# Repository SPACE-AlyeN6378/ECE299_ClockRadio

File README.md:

# Raspberry Pi Pico: Clock Radio
Clock radio is driven by Raspberry Pi Pico
## Configuration
### NORMAL MODE

- Button 1 - Mute
- Button 2 - Toggle 12-24 hour format
- Button 3 - Set time
- Button 4 - Set alarm
- Rotary button - Toggle between changing frequency/Volume 
- Turn knob - Change frequency/volume

### SET TIME MODE

- Button 1 - Menu Left
- Button 2 - Menu Right 
- Button 3 - Cancel
- Button 4 - Cancel setting & change alarm
- Rotary button - Confirm
- Turn knob - Change time

### SET ALARM MODE

- Button 1 - Menu Left
- Button 2 - Menu Right 
- Button 3 - Time settings
- Button 4 - Alarm on/off
- Rotary button - Confirm and exit
- Turn knob - Change alarm time

### WHILE ALARM IS RINGING

- Button 1 - Stop alarm
- Button 2 - Snooze

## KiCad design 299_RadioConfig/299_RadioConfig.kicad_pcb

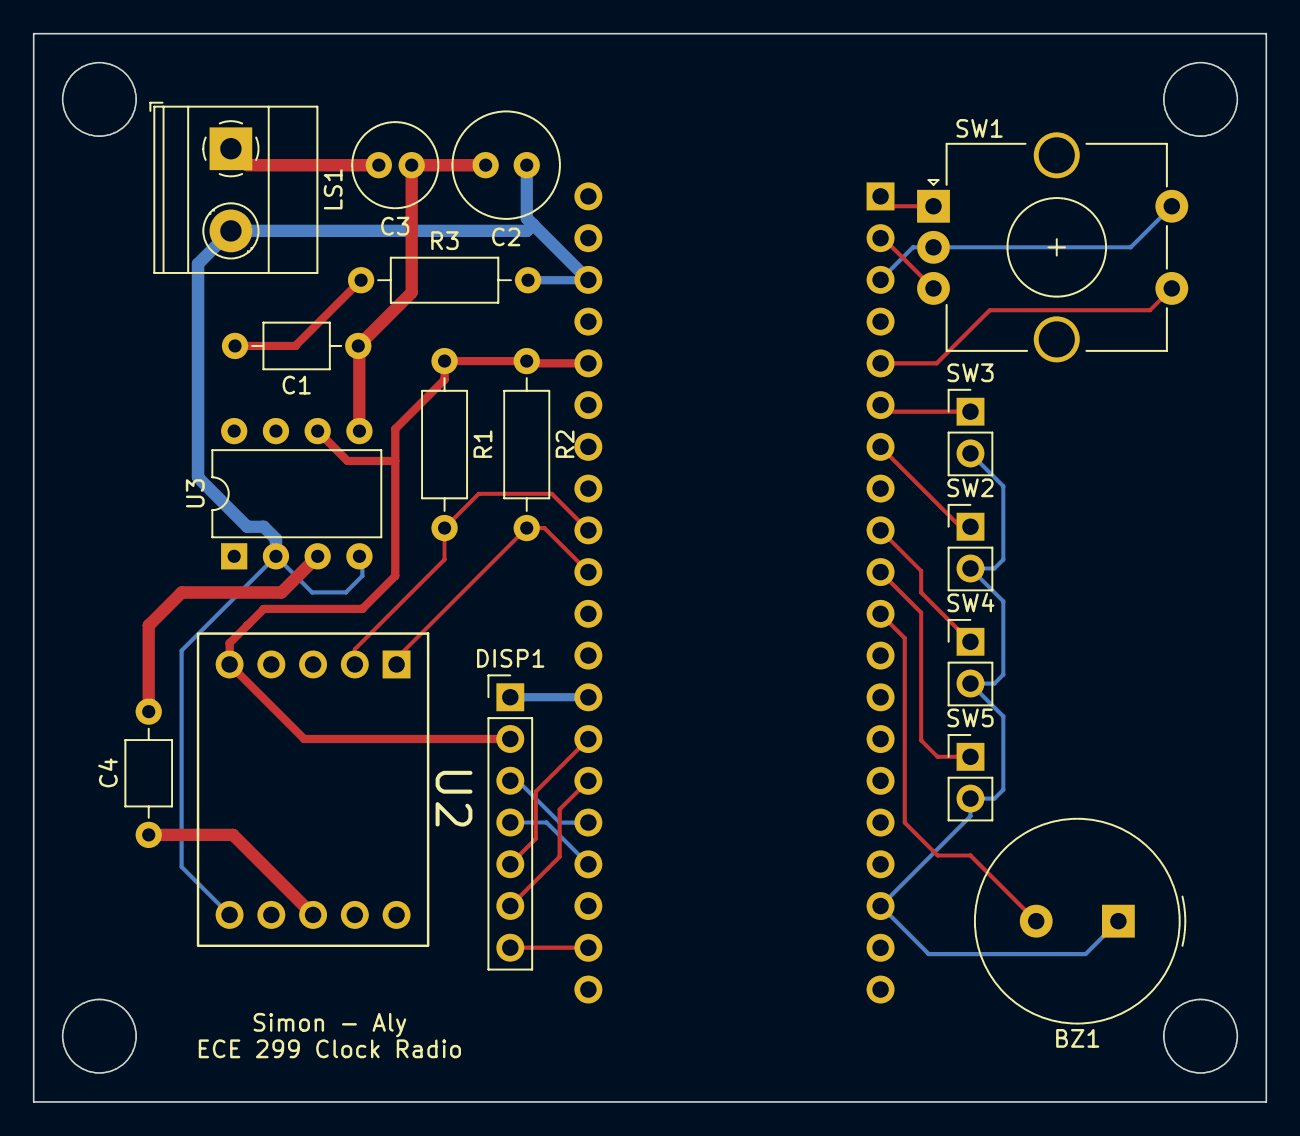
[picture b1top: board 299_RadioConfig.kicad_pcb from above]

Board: 2 copper layers, 75.0 x 65.0 mm, 18 parts (1 on the bottom side), 22 nets.

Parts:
BZ1: Buzzer; Buzzer_TDK_PS1240P02BT_D12.2mm_H6.5mm
C1, C4: .1u; C_Axial_L3.8mm_D2.6mm_P7.50mm_Horizontal
C2: 470u; C_Radial_D6.3mm_H11.0mm_P2.50mm
C3: 470u; C_Radial_D5.0mm_H11.0mm_P2.00mm
DISP1: OLED Display; PinHeader_1x07_P2.54mm_Vertical
LS1: Speaker; TerminalBlock_Phoenix_MKDS-1,5-2_1x02_P5.00mm_Horizontal
R1, R2: 2k; R_Axial_DIN0207_L6.3mm_D2.5mm_P10.16mm_Horizontal
R3: 10; R_Axial_DIN0207_L6.3mm_D2.5mm_P10.16mm_Horizontal
SW1: Bourns PEC11R; RotaryEncoder_Alps_EC12E-Switch_Vertical_H20mm_CircularMoun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
SW2, SW3, SW4, SW5: SW_Push; PinHeader_1x02_P2.54mm_Vertical
U1: RPi_Pico_TH
U2: RDA5807M_Module; RDA5807M_Module_TH
U3: LM386; DIP-8_W7.62mm

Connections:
GND: BZ1.1 (-), C2.1, DISP1.1 (VSS/GND), LS1.2, R3.2, SW1.C, SW1.S1, SW2.2, SW3.2, SW4.2, SW5.2, U1.3 (GND), U1.18 (GND), U1.28 (GND), U1.38 (GND), U2.6 (GND), U3.2 (-), U3.4 (GND)
unnamed: C1.1, C2.2, C3.1, U3.5
unnamed: C1.2, R3.1
unnamed: C3.2, LS1.1
unnamed: C4.1, U2.8 (LOUT)
unnamed: C4.2, U3.3 (+)
unnamed: DISP1.2 (VDD), R1.1, R2.1, U1.36 (3V3), U2.5 (VDD), U3.6 (V+)
unnamed: DISP1.3 (SCLK), U1.24 (GP18)
unnamed: DISP1.4 (SDA), U1.25 (GP19)
unnamed: DISP1.5 (RES), U1.27 (GP21)
unnamed: DISP1.6 (DC), U1.26 (GP20)
unnamed: DISP1.7 (CS), U1.22 (GP17)
unnamed: R1.2, U1.32 (GP27/ADC1), U2.2 (SCLK)
unnamed: R2.2, U1.31 (GP26/ADC0), U2.1 (SDIO)
unnamed: SW1.A, U1.1 (GP0)
unnamed: SW1.B, U1.2 (GP1)
unnamed: SW1.S2, U1.5 (GP3)
unnamed: SW2.1, U1.7 (GP5)
unnamed: SW3.1, U1.6 (GP4)
unnamed: SW4.1, U1.9 (GP6)
unnamed: SW5.1, U1.10 (GP7)
unnamed: BZ1.2 (+), U1.11 (GP8)

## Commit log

2023-06-07 Create Lab2
2023-06-07 Lab 2 Codes added
2023-06-07 Rename basicdisplay.py to counter.py
2023-06-24 codes redesigned as class structures
2023-07-04 Updated Radio Config, as ordered from JLCPCB
2023-07-18 Update README.md
    Config updated
2023-07-21 Codes finalized
2023-07-26 Solidworks files
    Inclusion of parts, assembly, and drawing outlining relevant dimensions.
2023-07-26 Solidworks files moved in folder
2023-07-26 3D Files moved to folder
2023-07-26 STL added for preview
